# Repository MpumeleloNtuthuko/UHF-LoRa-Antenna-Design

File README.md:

# UHF Antenna Design for LoRa Applications (Project FS04)

[-blue.svg)](http://www.uct.ac.za/)

> **Author:** Mpumelelo Ntuthuko Mpanza (`MPNMPU002`)
> **Supervisor:** Dr. Francois Willem Schonken  
> **Institution:** Department of Electrical Engineering, University of Cape Town 

---

## 📌 Project Overview

Antenna design at ultra high frequencies 300 MHz to 3 GHz presents significant physical constraints, particularly within the 433 MHz and 868 MHz ISM bands utilized by Long Range (LoRa) Internet of Things deployments. Traditional quarter wavelength resonant elements 173.1 mm at 433 MHz and 86.4 mm at 868 MHz are frequently too large for compact modern device enclosures.

Compressing physical dimensions below quarter wave pushes these radiators into the Electrically Small Antenna domain (ka < 0.5). According to the Chu-Harrington limit, spatial reduction leads to an exponential increase in stored reactive near field energy, resulting in narrow operational bandwidths, low radiation resistances, and high sensitivity to dielectric loading.

This repository contains the complete computational electromagnetic simulation models FEKO, KiCAD PCB layout files, mechanical designs and empirical test data for four specialized, pretuned compact antenna topologies designed to provide future UCT LoRa developers with easily integrable PCB drop in components.

---

## 🗂️ Repository Structure

```text
UHF-LoRa-Antenna-Design/
│
├── Coplannar IFA/              # 433 MHz Coplanar Inverted F Antenna (CADFEKO & KiCAD files)
├── Helical/                    # 433 MHz & 868 MHz Normal-Mode Helical Antennas & 3D print models
├── Quarter_Wave_Monopole/      # 868 MHz Meandered Monopole Antenna (CADFEKO & ground plane models)
├── Spiral/                     # 868 MHz Planar Archimedean Spiral Antenna (CADFEKO & PCB files)
└── .gitignore

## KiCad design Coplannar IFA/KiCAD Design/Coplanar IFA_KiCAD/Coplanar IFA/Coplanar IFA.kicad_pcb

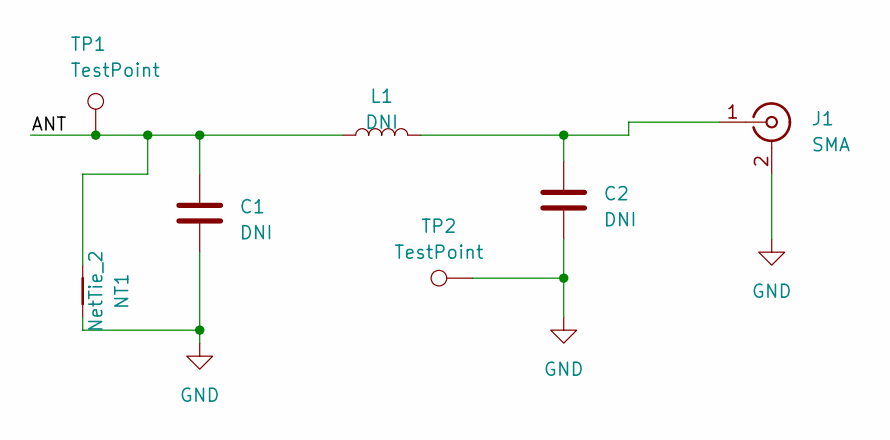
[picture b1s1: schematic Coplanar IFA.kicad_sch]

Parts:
C1, C2: DNI; C_0603_1608Metric
J1: SMA; SMA_Molex_73251-1153_EdgeMount_Horizontal
L1: DNI; L_0603_1608Metric
NT1: NetTie_2; NetTie-2_SMD_Pad0.5mm
TP1, TP2: TestPoint; TestPoint_Pad_D1.5mm

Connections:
/ANT: C1.1, L1.1, NT1.1, TP1.1
GND: C1.2, C2.2, J1.2 (Ext), NT1.2, TP2.1
unnamed: C2.1, J1.1 (In), L1.2

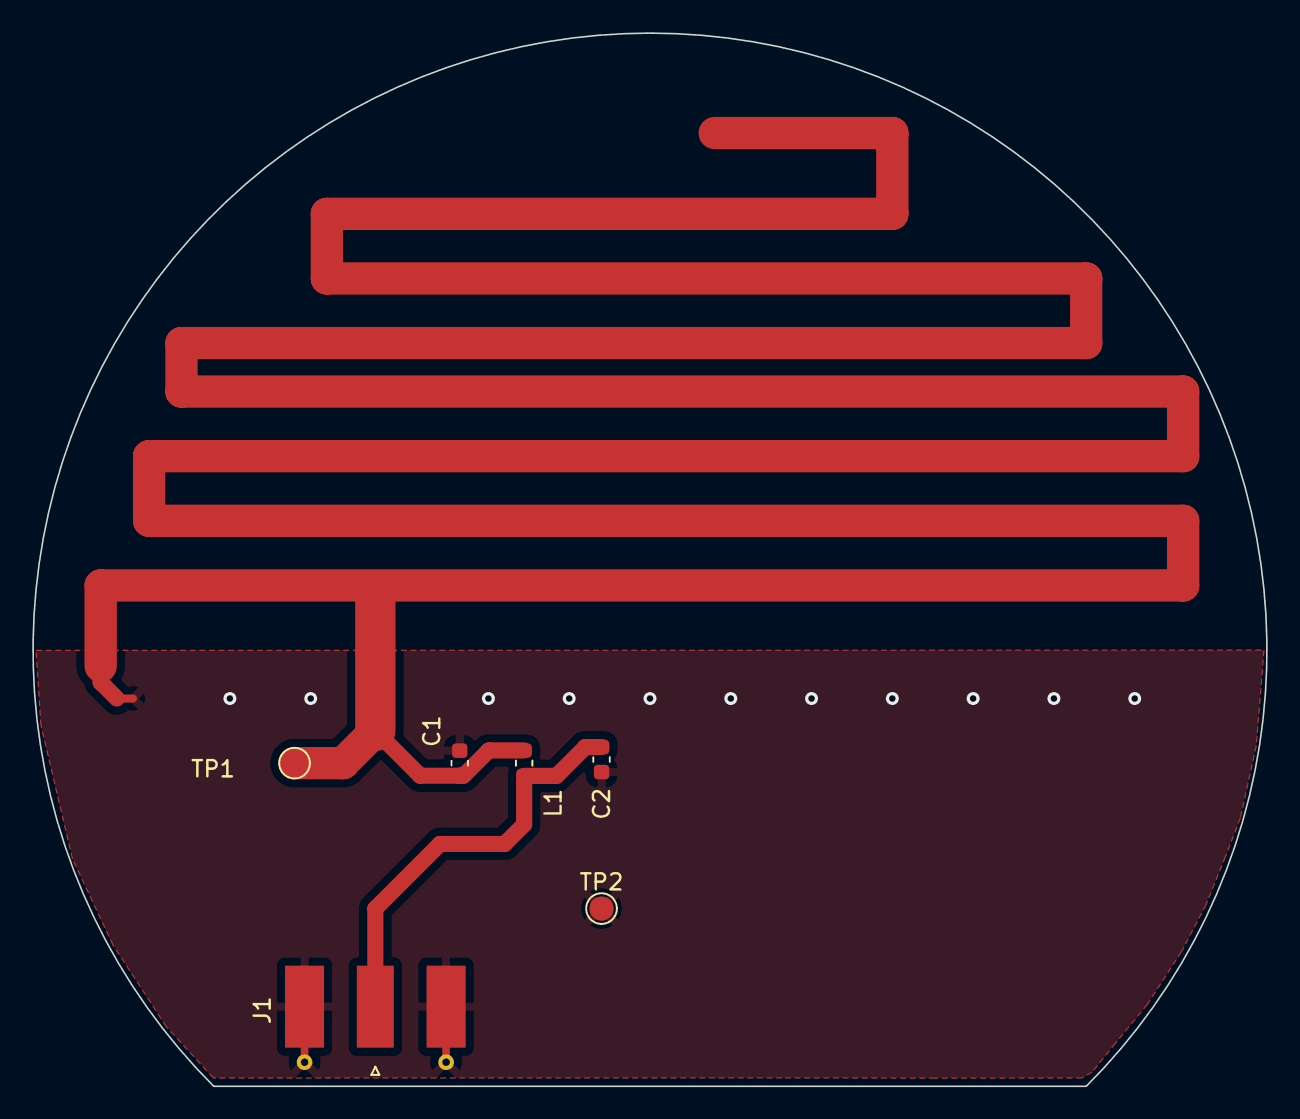
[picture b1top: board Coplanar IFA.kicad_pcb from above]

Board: 2 copper layers, 76.4 x 65.2 mm, 7 parts (0 on the bottom side), 3 nets.
